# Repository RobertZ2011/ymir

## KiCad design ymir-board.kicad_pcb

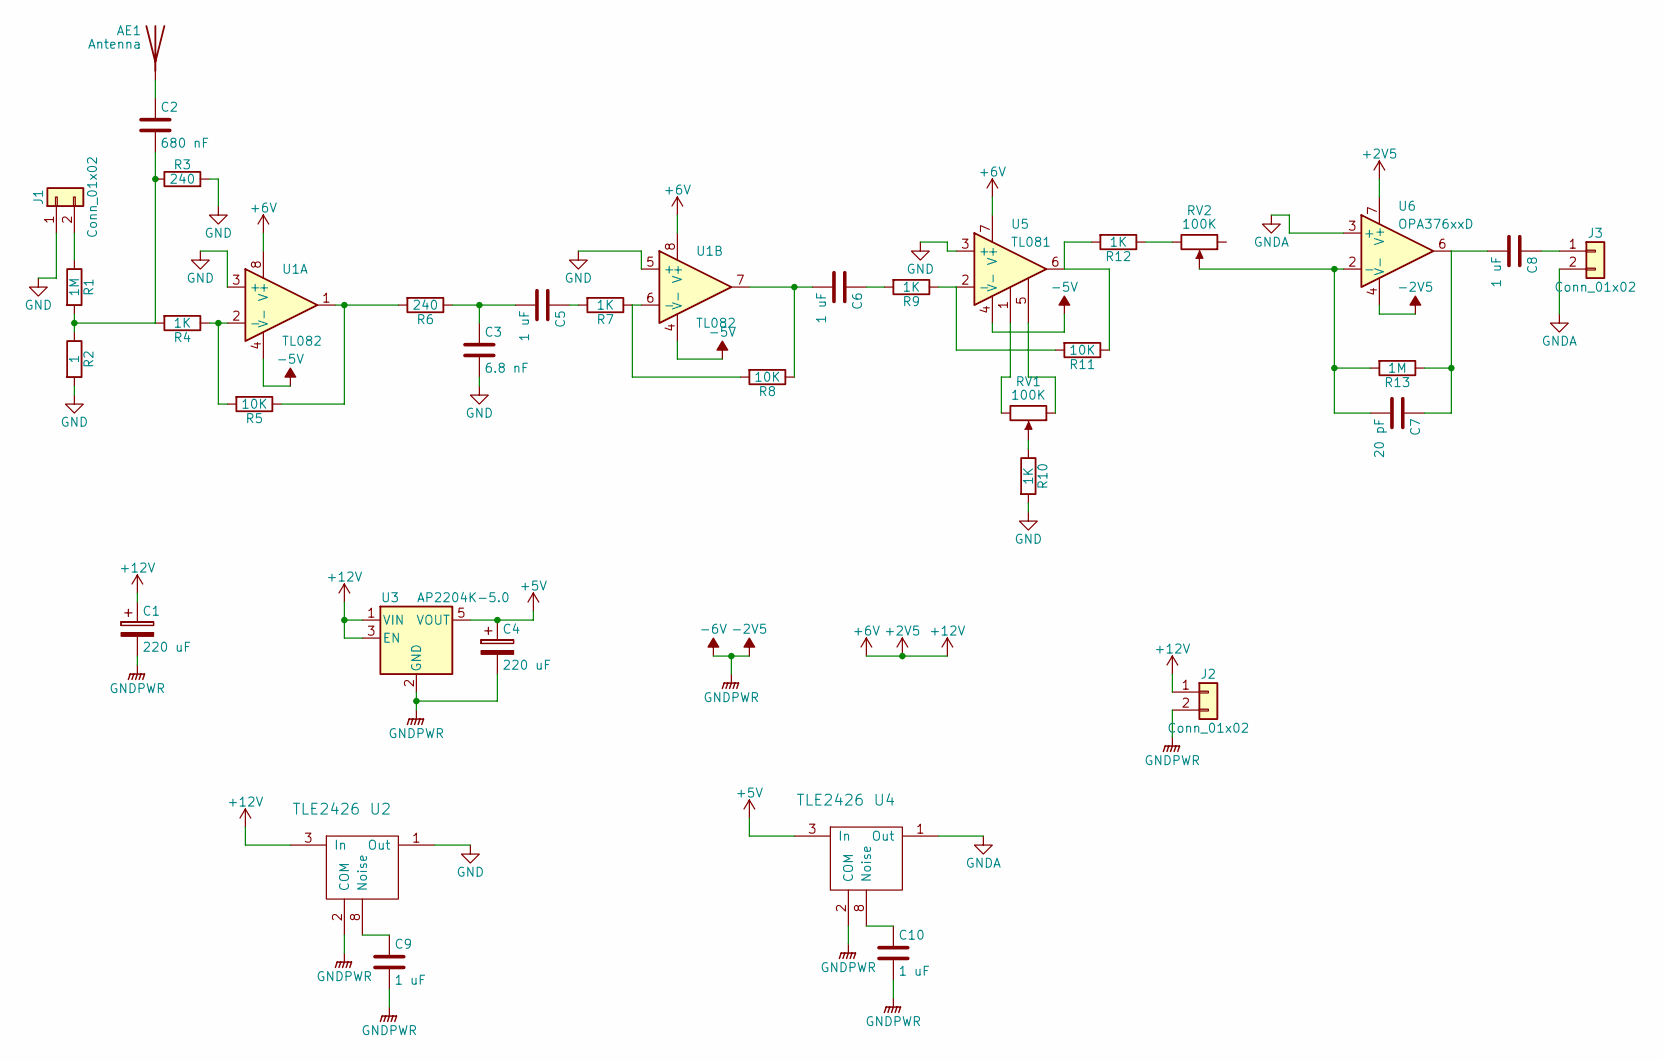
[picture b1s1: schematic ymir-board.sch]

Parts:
AE1: Antenna; Pin_Header_Straight_1x01_Pitch2.54mm
C1, C4: 220 uF; CP_Radial_D10.0mm_P2.50mm
C2: 680 nF; C_0805_HandSoldering
C3: 6.8 nF; C_0805_HandSoldering
C5, C6, C8, C9, C10: 1 uF; C_0805_HandSoldering
C7: 20 pF; C_0805_HandSoldering
J1, J2, J3: Conn_01x02; Pin_Header_Straight_1x02_Pitch2.54mm
R1, R13: 1M; R_0805_HandSoldering
R2: 1; R_0805_HandSoldering
R3, R6: 240; R_0805_HandSoldering
R4, R7, R9, R10, R12: 1K; R_0805_HandSoldering
R5, R8, R11: 10K; R_0805_HandSoldering
RV1, RV2: 100K; 23BR100KLFTR
U1: TL082; SOIC-8_3.9x4.9mm_Pitch1.27mm
U2, U4: TLE2426; SOIC-8_3.9x4.9mm_Pitch1.27mm
U3: AP2204K-5.0; SOT-23-5
U5: TL081; SOIC-8_3.9x4.9mm_Pitch1.27mm
U6: OPA376xxD; SOIC-8_3.9x4.9mm_Pitch1.27mm

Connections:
+5V: C4.1, U3.5 (VOUT), U4.3 (In)
+12V: C1.1, J2.1, U1.8 (V+), U2.3 (In), U3.1 (VIN), U3.3 (EN), U5.7 (V+), U6.7 (V+)
-2V5: C1.2, C4.2, C9.2, C10.2, J2.2, U2.2 (COM), U3.2 (GND), U4.2 (COM), U6.4 (V-)
-5V: U1.4 (V-), U5.4 (V-)
GND: C3.2, J1.1, R2.2, R3.2, R10.2, U1.3 (+), U1.5 (+), U2.1 (Out), U5.3 (+)
GNDA: J3.2, U4.1 (Out), U6.3 (+)
unnamed: AE1.1, C2.1
unnamed: C2.2, R1.2, R2.1, R3.1, R4.2
unnamed: C3.1, C5.2, R6.1
unnamed: C5.1, R7.2
unnamed: C6.1, R9.2
unnamed: C6.2, R8.1, U1.7
unnamed: C7.1, C8.2, R13.1, U6.6
unnamed: C7.2, R13.2, RV2.2, U6.2 (-)
unnamed: C8.1, J3.1
unnamed: C9.1, U2.8 (Noise)
unnamed: C10.1, U4.8 (Noise)
unnamed: J1.2, R1.1
unnamed: R4.1, R5.2, U1.2 (-)
unnamed: R5.1, R6.2, U1.1
unnamed: R7.1, R8.2, U1.6 (-)
unnamed: R10.1, RV1.2
unnamed: R11.1, R12.2, U5.6
unnamed: R9.1, R11.2, U5.2 (-)
unnamed: R12.1, RV2.3
unnamed: RV1.1, U5.5
unnamed: RV1.3, U5.1

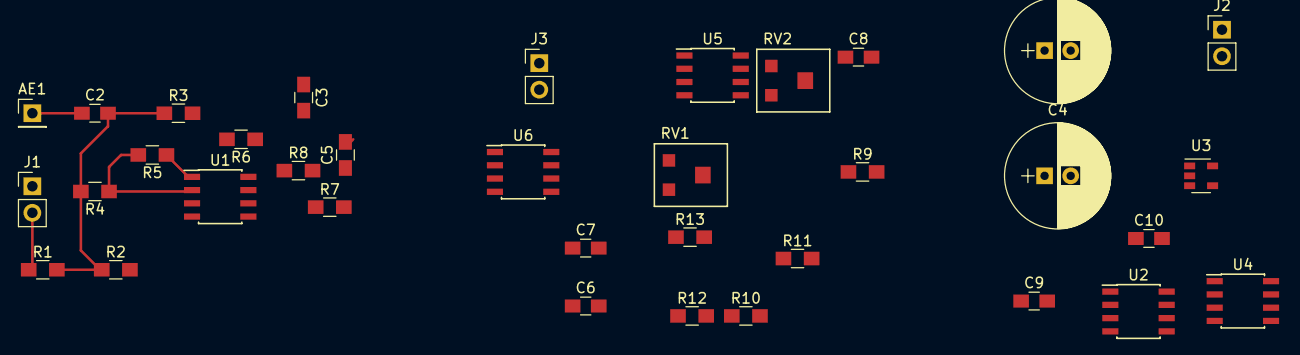
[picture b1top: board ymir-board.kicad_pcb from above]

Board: 2 copper layers, 35 parts (0 on the bottom side), 27 nets.
